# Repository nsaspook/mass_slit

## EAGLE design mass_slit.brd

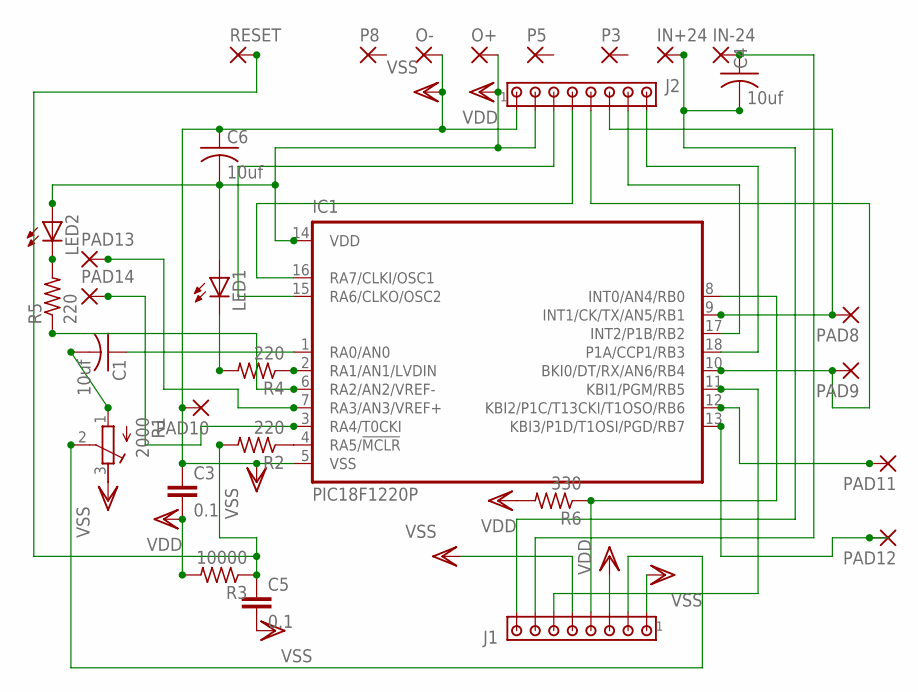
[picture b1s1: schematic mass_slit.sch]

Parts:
C1, C4, C6: 10uf; C025-040X050
C3, C5: 0.1; C5B2.5
IC1: PIC18F1220P; DIL18
IN+24: 1,6/0,9
IN-24: 1,6/0,9
J1, J2: MTA08-100; 10X08MTA
LED1, LED2: LED3MM
O+: 1,6/0,9
O-: 1,6/0,9
P3, P5, P8: 1,6/0,9
PAD8, PAD9, PAD10, PAD11, PAD12, PAD13, PAD14: 1,6/0,9
R1: 2000; RTRIM3339P
R2, R4, R5: 220; 0204V
R3: 10000; 0204V
R6: 330; 0204V
RESET: 1,6/0,9

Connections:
+24: C4.2, IN+24.1, J1.8
-24: C4.1, IN-24.1, J1.7
unnamed: IC1.10 (BKI0/DT/RX/AN6/RB4), J2.5, PAD9.1
unnamed: IC1.4 (RA5/!MCLR), R2.1
unnamed: C1.1, IC1.1 (RA0/AN0)
unnamed: C1.2, R1.1 (A)
unnamed: C5.1, R2.2, R3.1, RESET.1
unnamed: IC1.2 (RA1/AN1/LVDIN), R4.1
unnamed: IC1.8 (INT0/AN4/RB0), J1.4, R6.1
unnamed: IC1.13 (KBI3/P1D/T1OSI/PGD/RB7), PAD12.1
unnamed: J1.2, R1.2 (S)
unnamed: IC1.9 (INT1/CK/TX/AN5/RB1), J2.6, PAD8.1
unnamed: LED1.K (C), R4.2
unnamed: IC1.11 (KBI1/PGM/RB5), J1.6
unnamed: IC1.17 (INT2/P1B/RB2), J2.7
unnamed: IC1.18 (P1A/CCP1/RB3), J2.8
unnamed: IC1.16 (RA7/CLKI/OSC1), J2.4
unnamed: IC1.15 (RA6/CLKO/OSC2), J2.3
unnamed: IC1.12 (KBI2/P1C/T13CKI/T1OSO/RB6), PAD11.1
unnamed: IC1.7 (RA3/AN3/VREF+), PAD13.1
unnamed: IC1.3 (RA4/T0CKI), PAD14.1
unnamed: IC1.6 (RA2/AN2/VREF-), R5.1
unnamed: LED2.K (C), R5.2
VDD: C3.2, C6.2, IC1.14 (VDD), J1.3, J2.2, LED1.A, LED2.A, O+.1, R3.2, R6.2
VSS: C3.1, C5.2, C6.1, IC1.5 (VSS), J1.1, J1.5, J2.1, O-.1, PAD10.1, R1.3 (E)

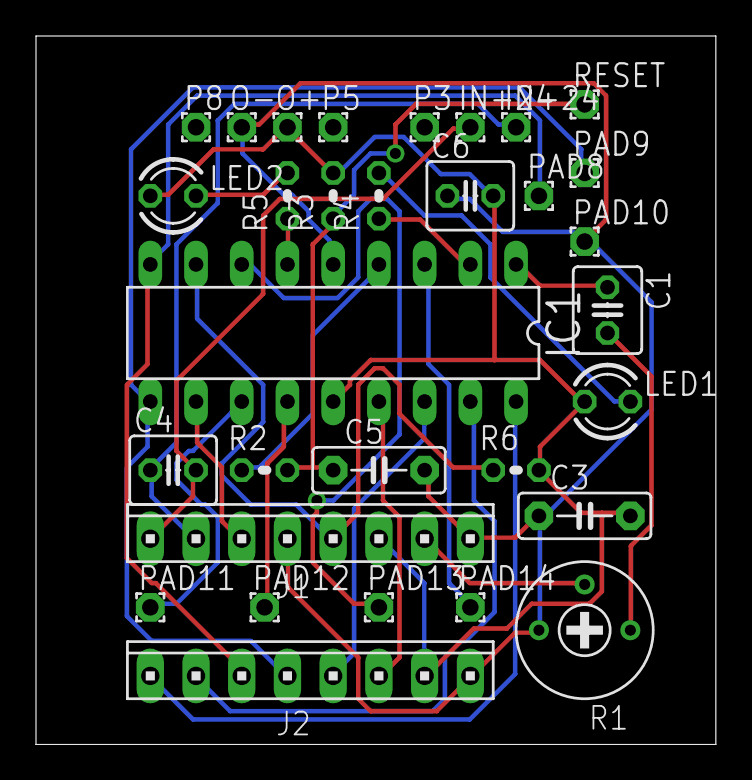
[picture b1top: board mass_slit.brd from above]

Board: 2 copper layers, 37.8 x 39.4 mm, 31 parts (0 on the bottom side), 25 nets.

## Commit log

2016-07-26 update all files
2019-01-28 updates, fast spinup at power up
